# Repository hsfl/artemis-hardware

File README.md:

<br>

# Artemis Cubesat Kit Hardware

This repository contains CAD models, Eagle designs, and thermal analysis for the Artemis Cubesat Kit V1.

For documentation and tutorials, visit our [project website](https://sites.google.com/hawaii.edu/artemiscubesatkit).

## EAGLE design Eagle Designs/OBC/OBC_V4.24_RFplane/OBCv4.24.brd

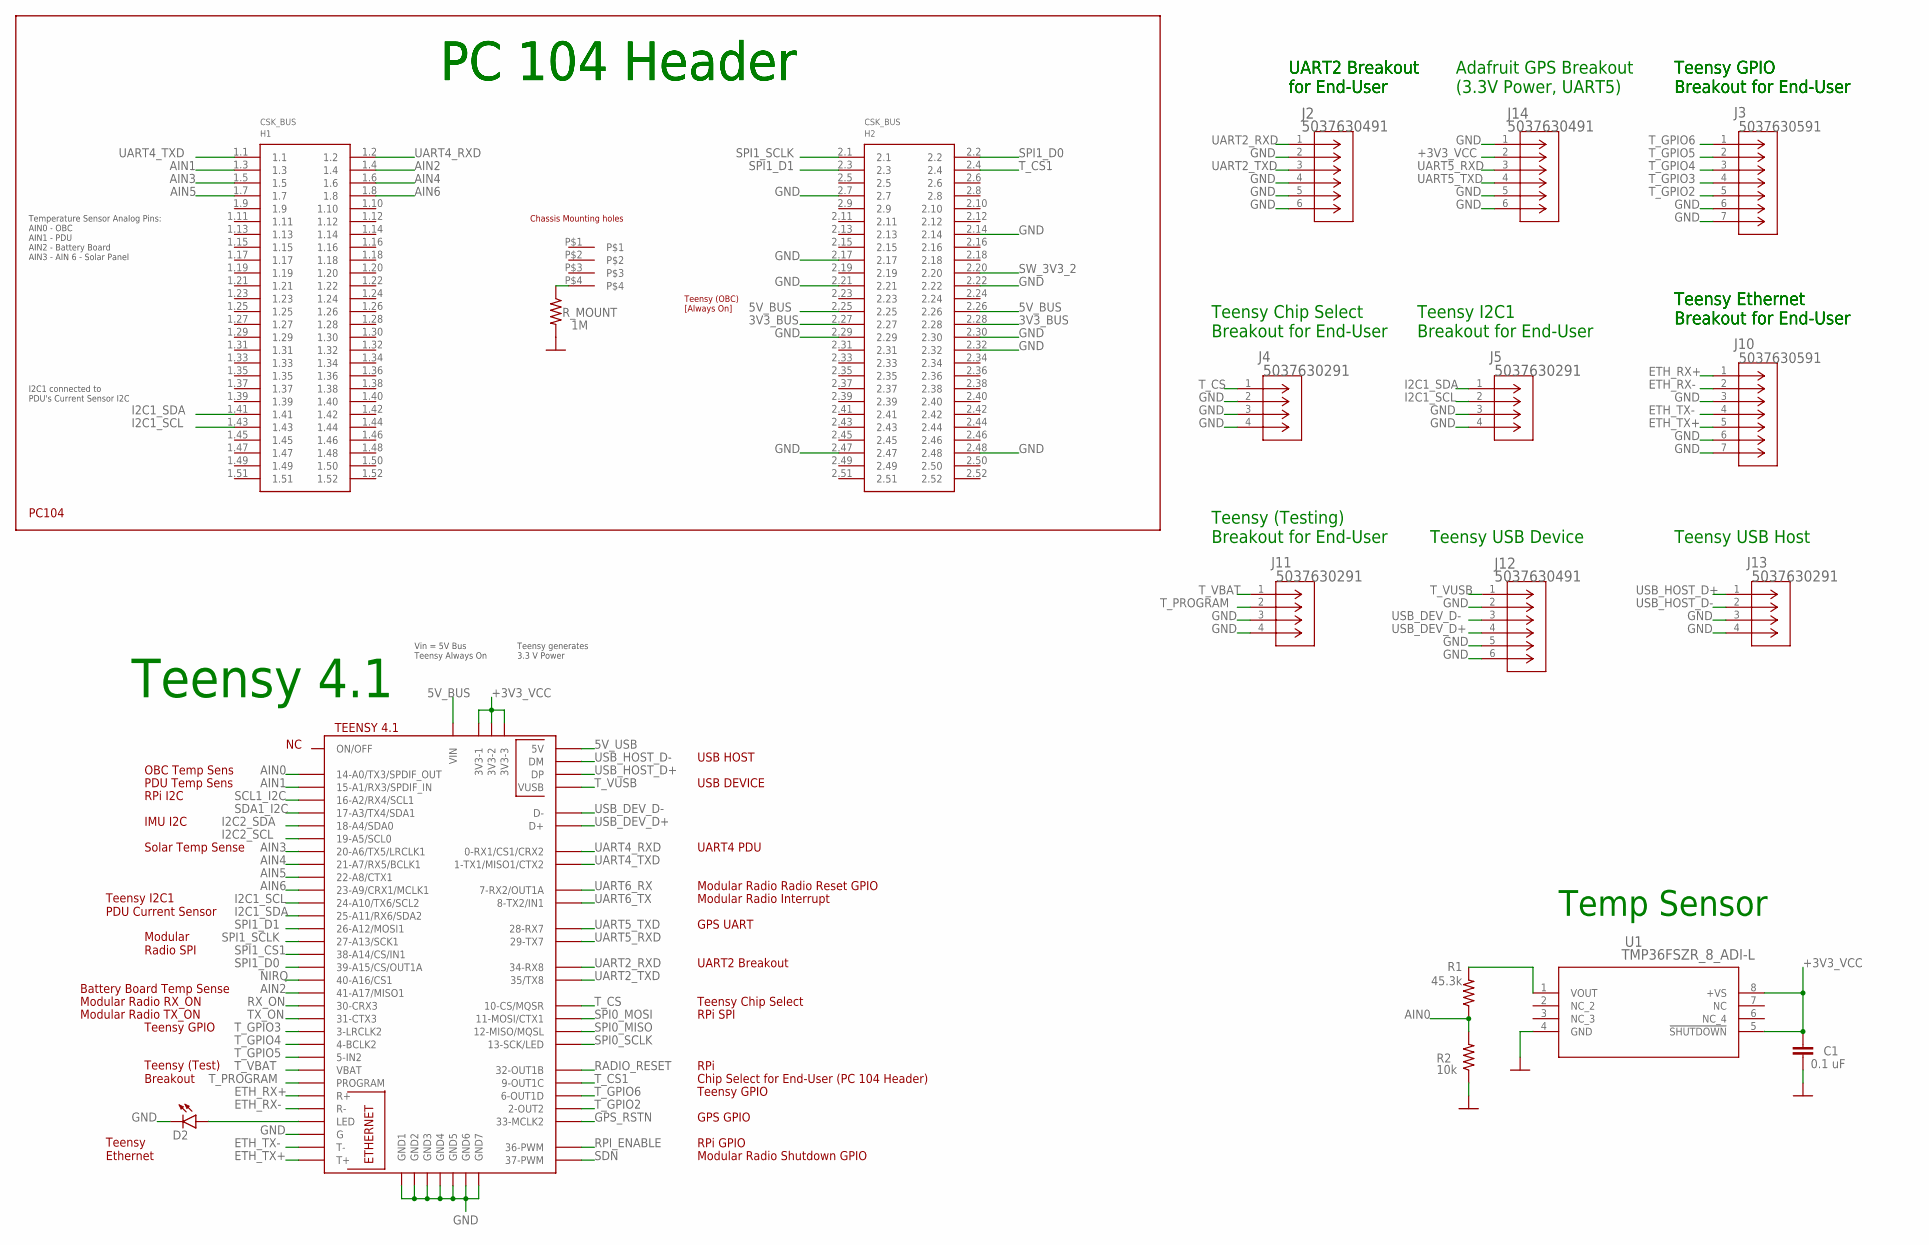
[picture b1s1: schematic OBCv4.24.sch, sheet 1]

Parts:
C1: 0.1 uF; 0805
D2: LEDCHIP-LED0603; CHIP-LED0603
H1: PC104_WCONN
J2, J12, J14: 5037630491; CON_5037630491
J3, J10: 5037630591; CON_5037630591
J4, J5, J11, J13: 5037630291; CON_5037630291
R1: 45.3k; 0805
R2: 10k; 0805
R_MOUNT: 1M; 0805
U1: TMP36FSZR_8_ADI-L; R_8_ADI-L
U$1: TEENSY41TEENSY; TEENSY41

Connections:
3V3_BUS: H1.2.27, H1.2.28; also elsewhere on the board
5V_BUS: H1.2.25, H1.2.26, U$1.VIN; also elsewhere on the board
5V_USB: U$1.+5V (5V)
+3V3_VCC: C1.1, J14.2, U1.5 (!SHUTDOWN), U1.8 (+VS), U$1.3V3-1, U$1.3V3-2, U$1.3V3-3; also elsewhere on the board
AIN0: R1.1, R2.2, U$1.14-A0/TX3/SPDIF_OUT
AIN1: H1.1.3, U$1.15-A1/RX3/SPDIF_IN
AIN2: H1.1.4, U$1.41-A17/MISO1
AIN3: H1.1.5, U$1.20-A6/TX5/LRCLK1
AIN4: H1.1.6, U$1.21-A7/RX5/BCLK1
AIN5: H1.1.7, U$1.22-A8/CTX1
AIN6: H1.1.8, U$1.23-A9/CRX1/MCLK1
ETH_RX+: J10.1, U$1.R+
ETH_RX-: J10.2, U$1.R-
ETH_TX+: J10.5, U$1.T+
ETH_TX-: J10.4, U$1.T-
GND: C1.2, D2.C, H1.2.7, H1.2.14, H1.2.17, H1.2.21, H1.2.22, H1.2.29, H1.2.30, H1.2.32, H1.2.47, H1.2.48, J2.2, J2.4, J2.5, J2.6, J3.6, J3.7, J4.2, J4.3, J4.4, J5.3, J5.4, J10.3, J10.6, J10.7, J11.3, J11.4, J12.2, J12.5, J12.6, J13.3, J13.4, J14.1, J14.5, J14.6, R2.1, R_MOUNT.2, U1.4 (GND), U$1.G, U$1.GND (GND7), U$1.GND1, U$1.GND2, U$1.GND3, U$1.GND4, U$1.GND5, U$1.GND6; also elsewhere on the board
GPS_RSTN: U$1.33-MCLK2; also elsewhere on the board
I2C1_SCL: H1.1.43, J5.2, U$1.24-A10/TX6/SCL2
I2C1_SDA: H1.1.41, J5.1, U$1.25-A11/RX6/SDA2
I2C2_SCL: U$1.19-A5/SCL0; also elsewhere on the board
I2C2_SDA: U$1.18-A4/SDA0; also elsewhere on the board
unnamed: D2.A, U$1.LED
unnamed: R1.2, U1.1 (VOUT)
unnamed: H1.P$4, R_MOUNT.1
NIRQ: U$1.40-A16/CS1; also elsewhere on the board
RADIO_RESET: U$1.32-OUT1B; also elsewhere on the board
RPI_ENABLE: U$1.36-PWM; also elsewhere on the board
RX_ON: U$1.30-CRX3; also elsewhere on the board
SCL1_I2C: U$1.16-A2/RX4/SCL1; also elsewhere on the board
SDA1_I2C: U$1.17-A3/TX4/SDA1; also elsewhere on the board
SDN: U$1.37-PWM; also elsewhere on the board
SPI0_MISO: U$1.12-MISO/MQSL; also elsewhere on the board
SPI0_MOSI: U$1.11-MOSI/CTX1; also elsewhere on the board
SPI0_SCLK: U$1.13-SCK/LED; also elsewhere on the board
SPI1_CS1: U$1.38-A14/CS/IN1; also elsewhere on the board
SPI1_D0: H1.2.2, U$1.39-A15/CS/OUT1A; also elsewhere on the board
SPI1_D1: H1.2.3, U$1.26-A12/MOSI1; also elsewhere on the board
SPI1_SCLK: H1.2.1, U$1.27-A13/SCK1; also elsewhere on the board
SW_3V3_2: H1.2.20; also elsewhere on the board
TX_ON: U$1.31-CTX3; also elsewhere on the board
T_CS: J4.1, U$1.10-CS\MQSR (10-CS/MQSR)
T_CS1: H1.2.4, U$1.9-OUT1C
T_GPIO2: J3.5, U$1.2-OUT2
T_GPIO3: J3.4, U$1.3-LRCLK2
T_GPIO4: J3.3, U$1.4-BCLK2
T_GPIO5: J3.2, U$1.5-IN2
T_GPIO6: J3.1, U$1.6-OUT1D
T_PROGRAM: J11.2, U$1.PROGRAM
T_VBAT: J11.1, U$1.VBAT
T_VUSB: J12.1, U$1.VUSB
UART2_RXD: J2.1, U$1.34-RX8
UART2_TXD: J2.3, U$1.35-TX8 (35/TX8)
UART4_RXD: H1.1.2, U$1.0-RX1/CS1/CRX2
UART4_TXD: H1.1.1, U$1.1-TX1/MISO1/CTX2
UART5_RXD: J14.3, U$1.29-TX7; also elsewhere on the board
UART5_TXD: J14.4, U$1.28-RX7; also elsewhere on the board
UART6_RX: U$1.7-RX2/OUT1A; also elsewhere on the board
UART6_TX: U$1.8-TX2/IN1; also elsewhere on the board
USB_DEV_D+: J12.4, U$1.D+
USB_DEV_D-: J12.3, U$1.D-
USB_HOST_D+: J13.1, U$1.DP
USB_HOST_D-: J13.2, U$1.DM

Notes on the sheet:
Temp Sensor
PC 104 Header
Temperature Sensor Analog Pins: AIN0 - OBC AIN1 - PDU AIN2 - Battery Board AIN3 - AIN 6 - Solar Panel
UART2 Breakout for End-User
Teensy 4.1
Teensy GPIO Breakout for End-User
Teensy Chip Select Breakout for End-User
Teensy I2C1 Breakout for End-User
OBC Temp Sens
PDU Temp Sens
RPi I2C
IMU I2C
Solar Temp Sense
Teensy I2C1 PDU Current Sensor
Modular Radio SPI
Battery Board Temp Sense
Teensy GPIO
Teensy (Test) Breakout
Teensy Ethernet
RPi GPIO
GPS GPIO
RPi SPI
Teensy Chip Select
UART2 Breakout
GPS UART
Modular Radio Radio Reset GPIO
UART4 PDU
USB HOST
USB DEVICE
Teensy Ethernet Breakout for End-User
Teensy (Testing) Breakout for End-User
Teensy USB Device
Teensy USB Host
Teensy (OBC) [Always On]
Vin = 5V Bus Teensy Always On
Teensy generates 3.3 V Power
Adafruit GPS Breakout (3.3V Power, UART5)
Modular Radio Interrupt
I2C1 connected to PDU's Current Sensor I2C
Chip Select for End-User (PC 104 Header)

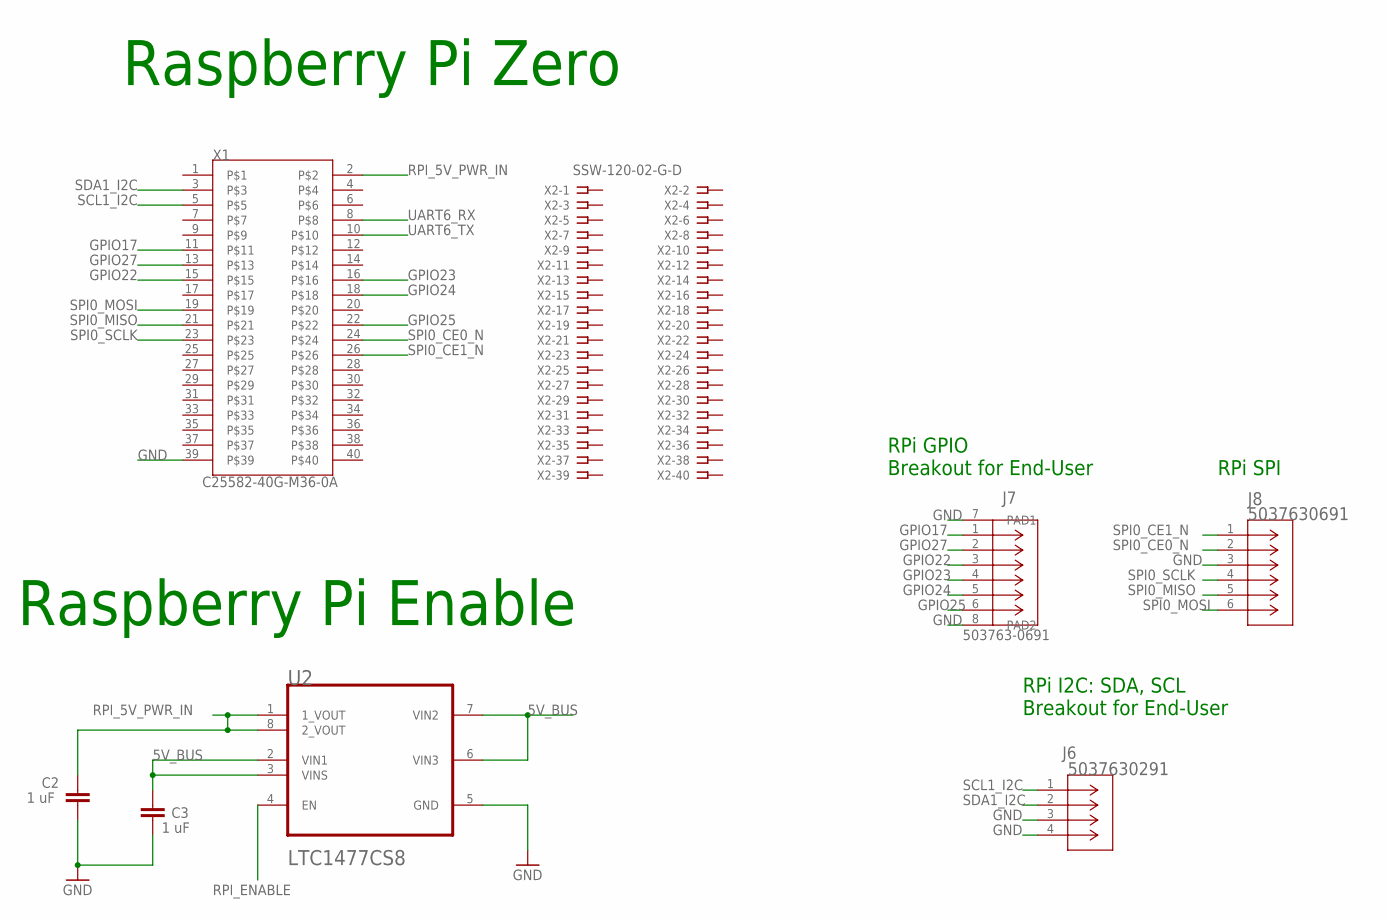
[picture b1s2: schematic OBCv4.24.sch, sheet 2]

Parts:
C2, C3: 1 uF; 0805
J6: 5037630291; CON_5037630291
J7: 503763-0691; CONN_503763-0691_MOL
J8: 5037630691; CONN_503763-0691_MOL
U2: LTC1477CS8LINEAR_TECHNOLOGY_LTC1477CS8_0_2; LINEAR_TECHNOLOGY_LTC1477CS8_2
X1: C25582-40G-M36-0A; ADAFRUIT_C25582-40G-M36-0A_0
X2: SSW-120-02-G-D

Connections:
5V_BUS: C3.1, U2.2 (VIN1), U2.3 (VINS), U2.6 (VIN3), U2.7 (VIN2); also elsewhere on the board
GND: C2.2, C3.2, J6.3, J6.4, J7.7 (PAD1), J7.8 (PAD2), J8.3, U2.5 (GND), X1.39; also elsewhere on the board
GPIO17: J7.1, X1.11
GPIO22: J7.3, X1.15
GPIO23: J7.4, X1.16
GPIO24: J7.5, X1.18
GPIO25: J7.6, X1.22
GPIO27: J7.2, X1.13
RPI_5V_PWR_IN: C2.1, U2.1 (1_VOUT), U2.8 (2_VOUT), X1.2
RPI_ENABLE: U2.4 (EN); also elsewhere on the board
SCL1_I2C: J6.1, X1.5; also elsewhere on the board
SDA1_I2C: J6.2, X1.3; also elsewhere on the board
SPI0_CE0_N: J8.2, X1.24
SPI0_CE1_N: J8.1, X1.26
SPI0_MISO: J8.5, X1.21; also elsewhere on the board
SPI0_MOSI: J8.6, X1.19; also elsewhere on the board
SPI0_SCLK: J8.4, X1.23; also elsewhere on the board
UART6_RX: X1.8; also elsewhere on the board
UART6_TX: X1.10; also elsewhere on the board

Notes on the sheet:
Raspberry Pi Zero
Raspberry Pi Enable
RPi I2C: SDA, SCL Breakout for End-User
RPi GPIO Breakout for End-User
RPi SPI

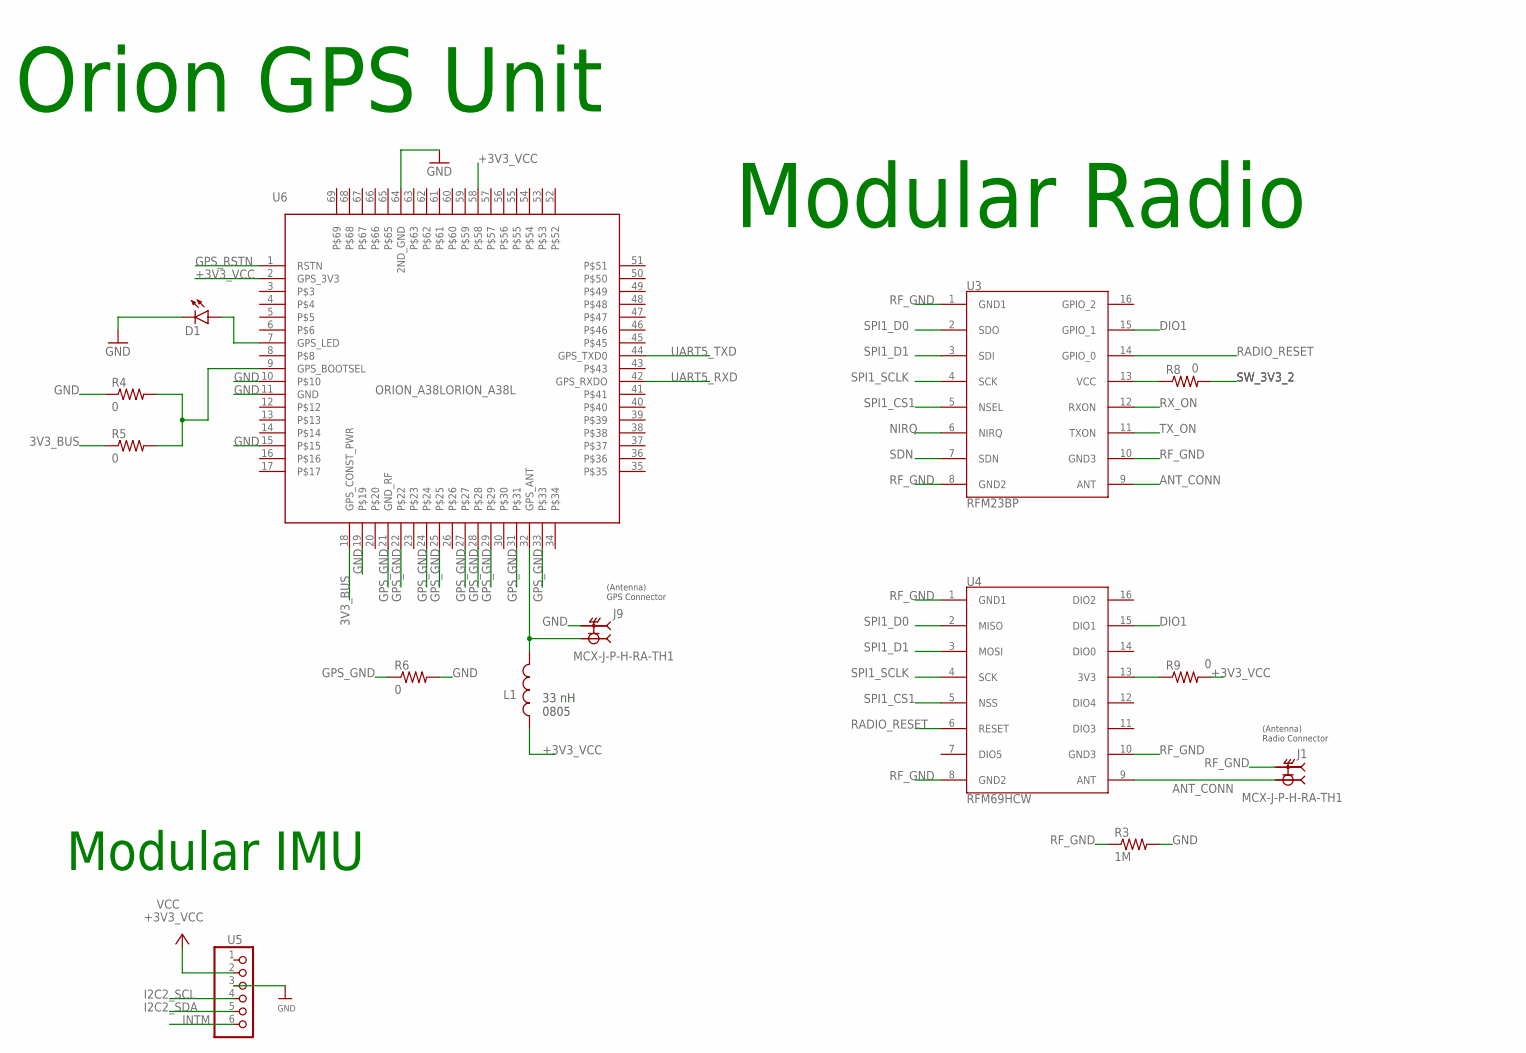
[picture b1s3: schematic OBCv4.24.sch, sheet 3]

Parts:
D1: LEDCHIP-LED0603; CHIP-LED0603
J1, J9: MCX-J-P-H-RA-TH1; SAMTEC_MCX-J-P-H-RA-TH1
L1: AIMC-0805-2N2S-T; INDC2012X105N
R3: 1M; 0805
R4, R5, R6: 0; 0805
R8, R9: 0; R2512
U3: RFM23BP
U4: RFM69HCW
U5: HEADER-1X670MIL; 1X06_ROUND_70
U6: ORION_A38LORION_A38L; ORION_A38L

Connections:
3V3_BUS: R5.1, U6.18 (GPS_CONST_PWR); also elsewhere on the board
+3V3_VCC: L1.1, R9.2, U5.2, U6.2 (GPS_3V3), U6.58; also elsewhere on the board
ANT_CONN: J1.1, U3.9 (ANT), U4.9 (ANT)
DIO1: U3.15 (GPIO_1), U4.15 (DIO1)
GND: D1.C, J9.S1 (2), J9.S2 (2), J9.S3 (2), J9.S4 (2), R3.2, R4.1, R6.2, U5.3, U6.10, U6.11 (GND), U6.15, U6.19, U6.64 (2ND_GND); also elsewhere on the board
GPS_GND: R6.1, U6.21 (GND_RF), U6.22, U6.24, U6.25, U6.27, U6.28, U6.29, U6.31, U6.33
GPS_RSTN: U6.1 (RSTN); also elsewhere on the board
I2C2_SCL: U5.4; also elsewhere on the board
I2C2_SDA: U5.5; also elsewhere on the board
INTM: U5.6
unnamed: R8.1, U3.13 (VCC)
unnamed: R9.1, U4.13 (3V3)
unnamed: R4.2, R5.2, U6.9 (GPS_BOOTSEL)
unnamed: J9.1, L1.2, U6.32 (GPS_ANT)
unnamed: D1.A, U6.7 (GPS_LED)
NIRQ: U3.6 (NIRQ); also elsewhere on the board
RADIO_RESET: U3.14 (GPIO_0), U4.6 (RESET); also elsewhere on the board
RF_GND: J1.S1 (2), J1.S2 (2), J1.S3 (2), J1.S4 (2), R3.1, U3.1 (GND1), U3.8 (GND2), U3.10 (GND3), U4.1 (GND1), U4.8 (GND2), U4.10 (GND3)
RX_ON: U3.12 (RXON); also elsewhere on the board
SDN: U3.7 (SDN); also elsewhere on the board
SPI1_CS1: U3.5 (NSEL), U4.5 (NSS); also elsewhere on the board
SPI1_D0: U3.2 (SDO), U4.2 (MISO); also elsewhere on the board
SPI1_D1: U3.3 (SDI), U4.3 (MOSI); also elsewhere on the board
SPI1_SCLK: U3.4 (SCK), U4.4 (SCK); also elsewhere on the board
SW_3V3_2: R8.2; also elsewhere on the board
TX_ON: U3.11 (TXON); also elsewhere on the board
UART5_RXD: U6.42 (GPS_RXDO); also elsewhere on the board
UART5_TXD: U6.44 (GPS_TXD0); also elsewhere on the board

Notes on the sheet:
Orion GPS Unit
Modular Radio
Modular IMU
(Antenna) Radio Connector
(Antenna) GPS Connector
33 nH 0805

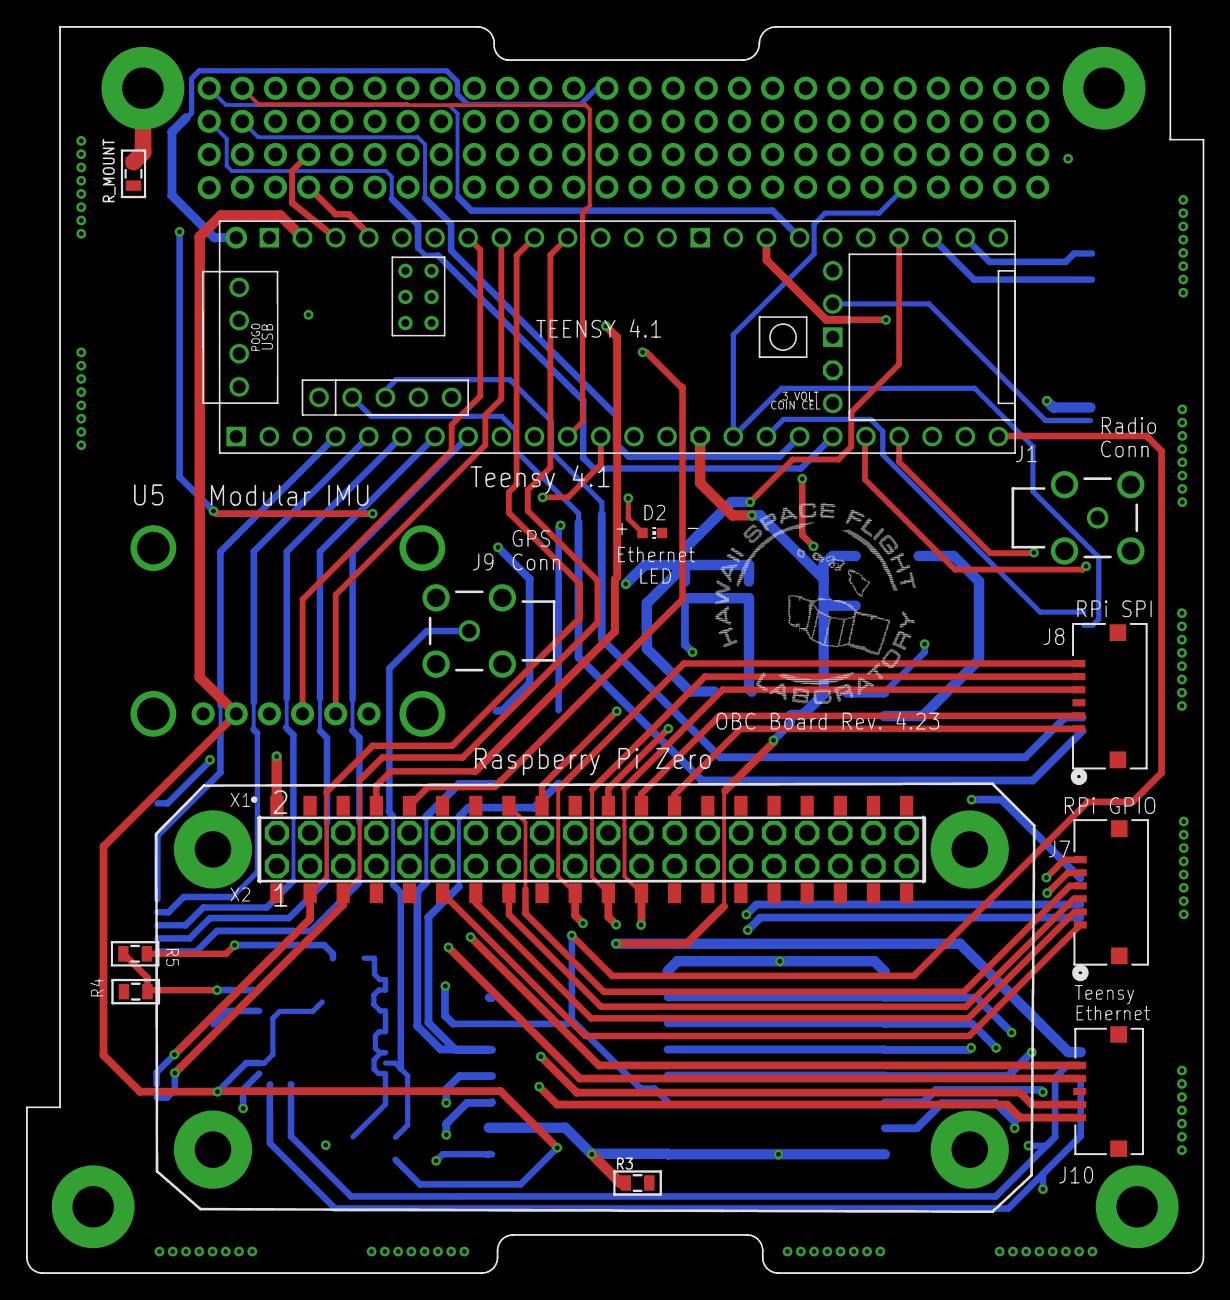
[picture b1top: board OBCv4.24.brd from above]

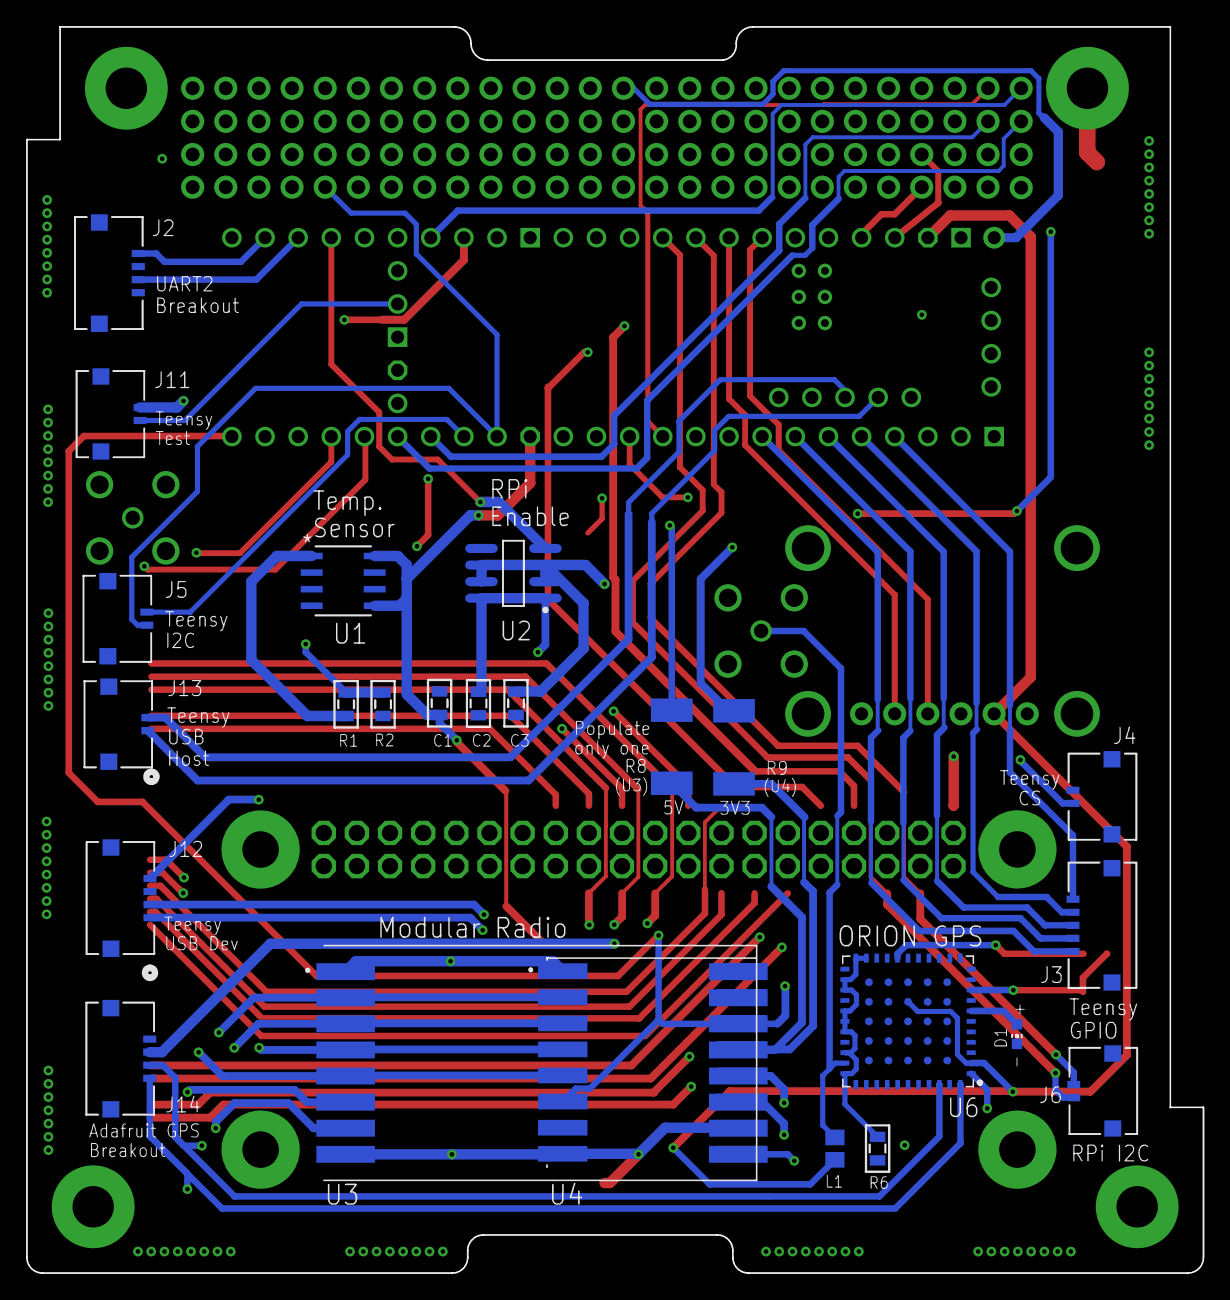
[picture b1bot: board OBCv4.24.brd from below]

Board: 4 copper layers, 90.2 x 95.5 mm, 39 parts (24 on the bottom side), 79 nets.

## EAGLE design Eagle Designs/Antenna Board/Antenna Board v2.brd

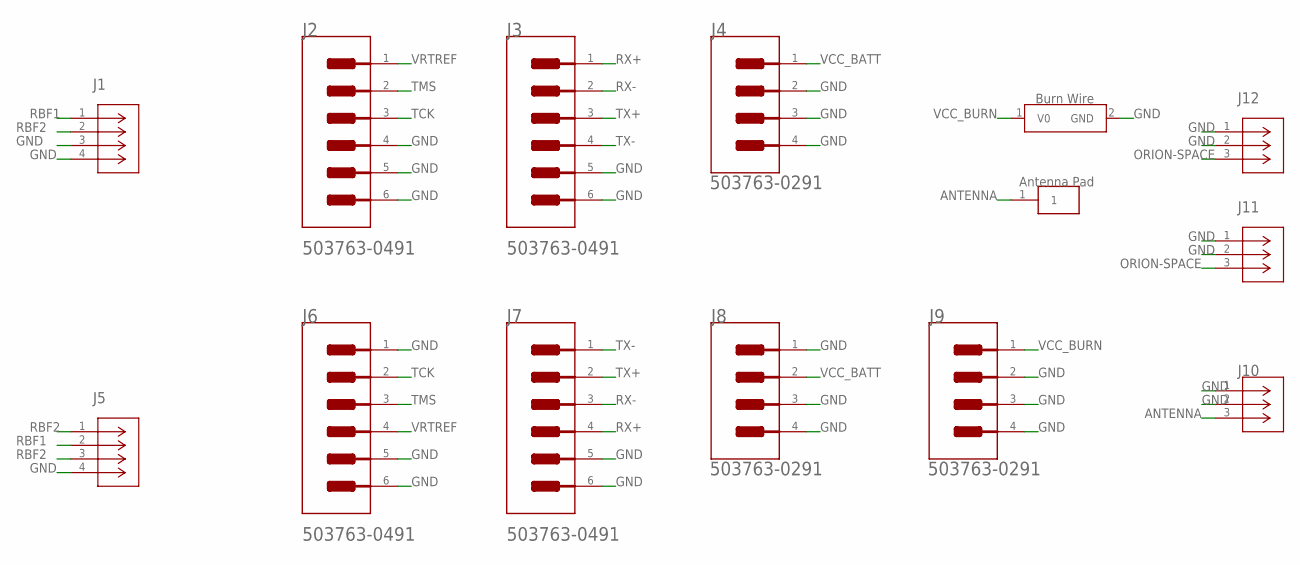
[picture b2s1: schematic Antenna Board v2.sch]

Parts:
J1, J5: 5037630291; CON_5037630291
J2, J3, J6, J7: MOLEX_503763-0491MOLEX_503763-0491_0_0; MOLEX_503763-0491_0
J4, J8, J9: MOLEX_503763-0291MOLEX_503763-0291_0_0; MOLEX_503763-0291_0
J10, J11, J12: U.FL-R-SMT-1(01); CONN_-SMT-1(01)
U$2: ANTENNA_PAD
U$3: BURNWIRE

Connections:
ANTENNA: J10.3, U$2.1
GND: J1.3, J1.4, J2.4, J2.5 (MNT_1), J2.6 (MNT_2), J3.5 (MNT_1), J3.6 (MNT_2), J4.2, J4.3 (MNT_1), J4.4 (MNT_2), J5.4, J6.1, J6.5 (MNT_1), J6.6 (MNT_2), J7.5 (MNT_1), J7.6 (MNT_2), J8.1, J8.3 (MNT_1), J8.4 (MNT_2), J9.2, J9.3 (MNT_1), J9.4 (MNT_2), J10.1, J10.2, J11.1, J11.2, J12.1, J12.2, U$3.2 (GND)
ORION-SPACE: J11.3, J12.3
RBF1: J1.1, J5.2
RBF2: J1.2, J5.1, J5.3
RX+: J3.1, J7.4
RX-: J3.2, J7.3
TCK: J2.3, J6.2
TMS: J2.2, J6.3
TX+: J3.3, J7.2
TX-: J3.4, J7.1
VCC_BATT: J4.1, J8.2
VCC_BURN: J9.1, U$3.1 (V0)
VRTREF: J2.1, J6.4

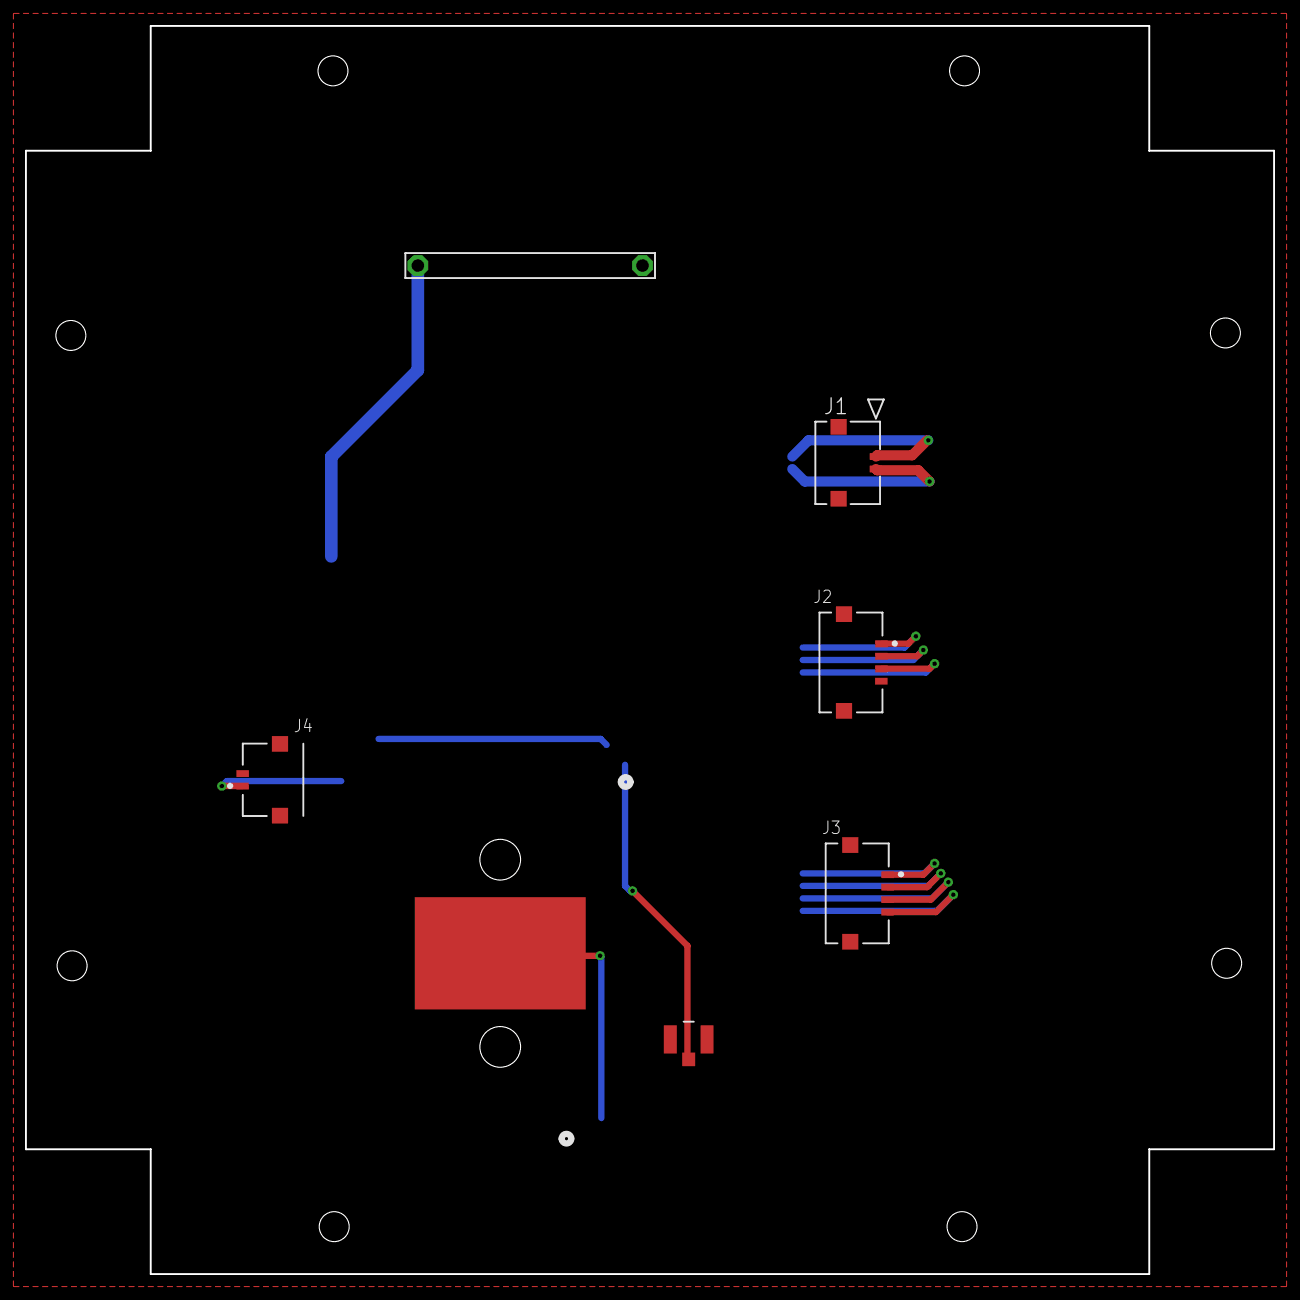
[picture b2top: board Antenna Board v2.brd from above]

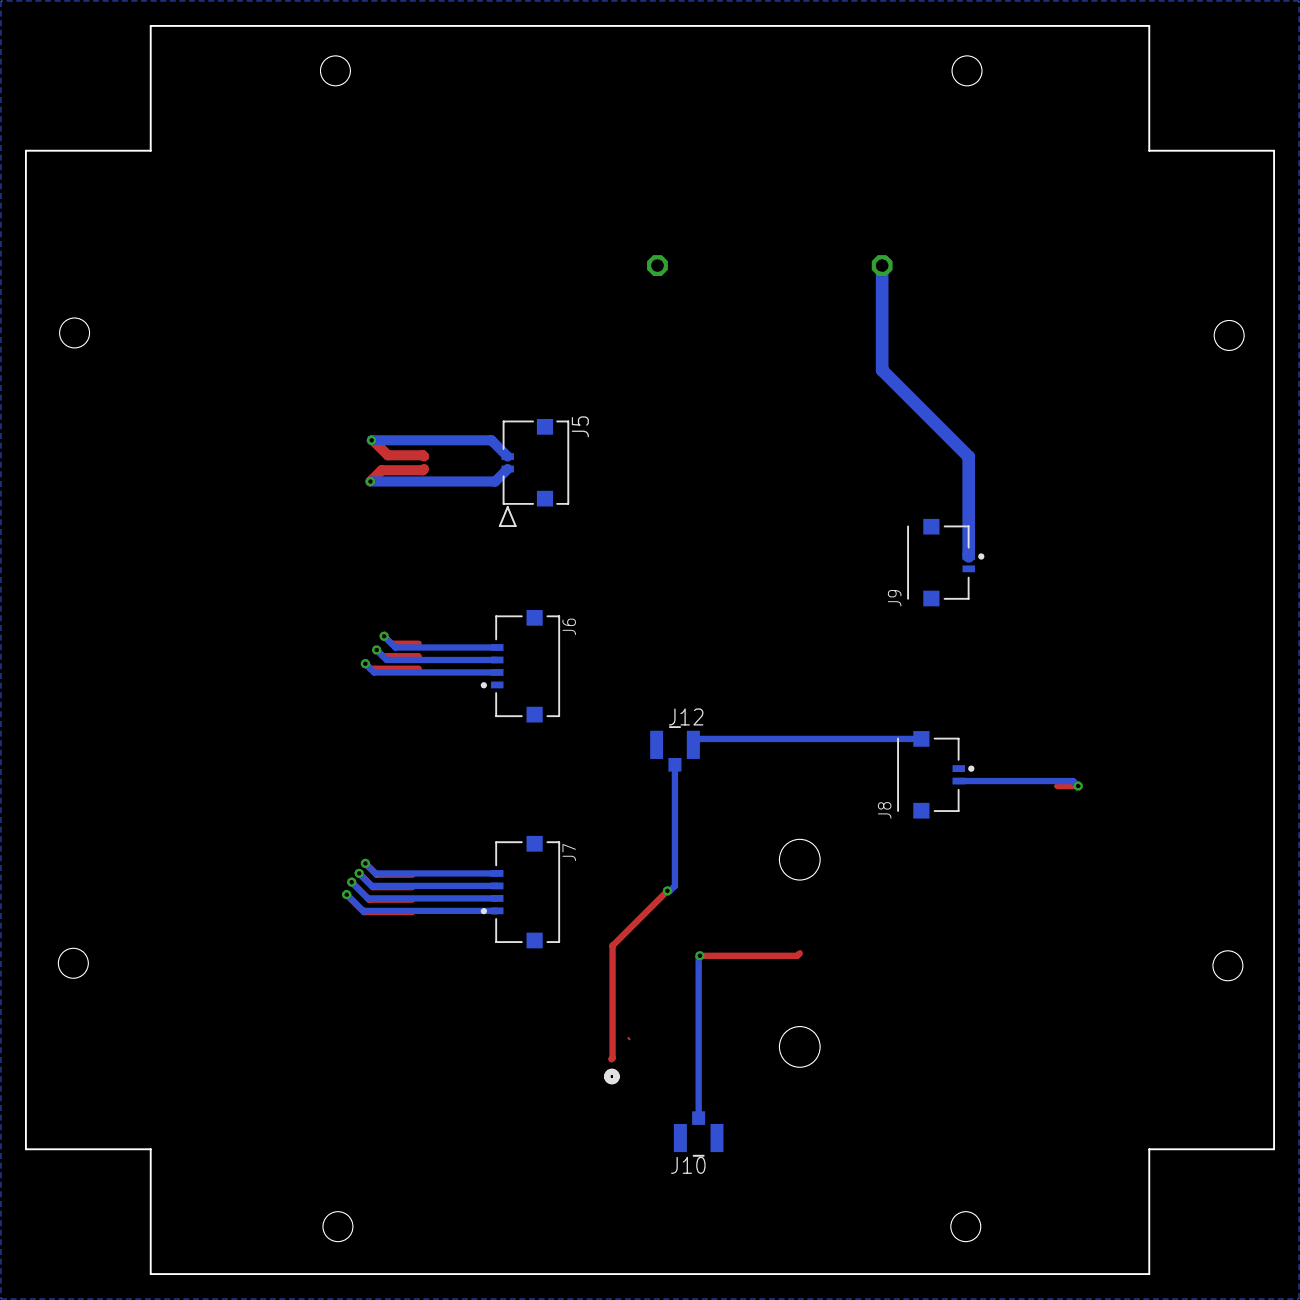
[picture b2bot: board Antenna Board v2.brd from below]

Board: 2 copper layers, 100.0 x 100.0 mm, 14 parts (7 on the bottom side), 14 nets.

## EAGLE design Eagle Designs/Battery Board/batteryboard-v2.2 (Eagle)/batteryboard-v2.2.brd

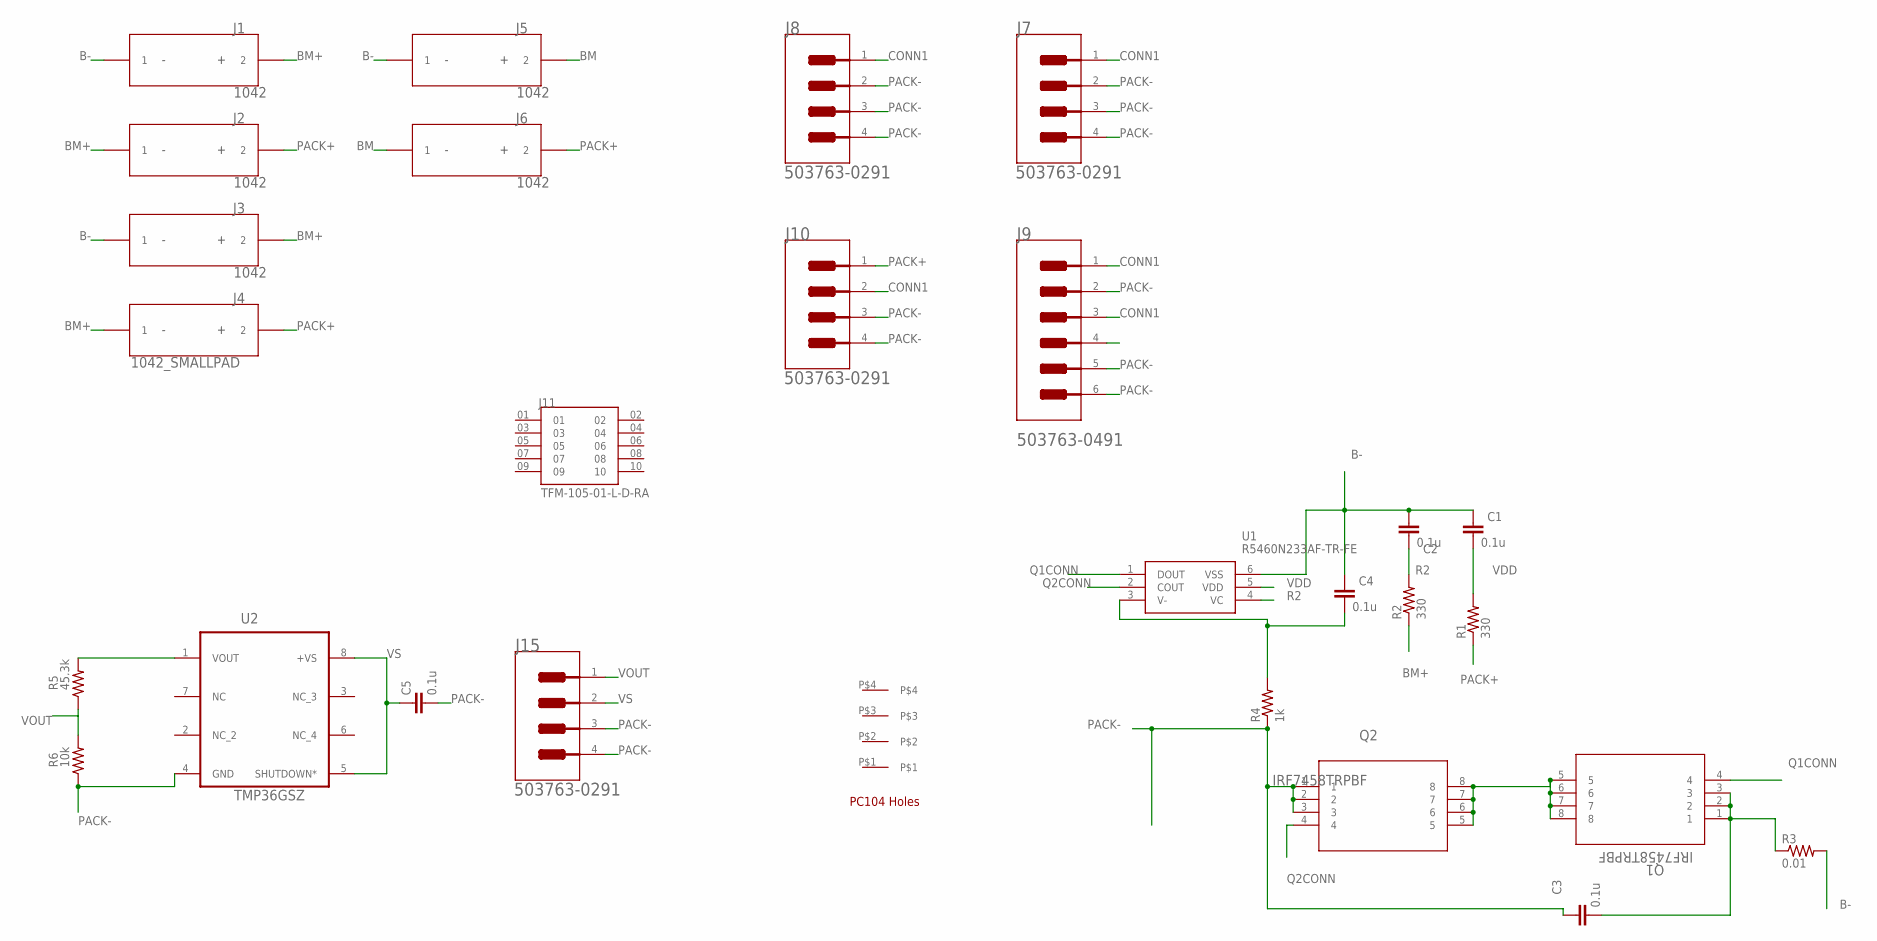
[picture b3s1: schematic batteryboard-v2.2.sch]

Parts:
C1, C2, C3, C4: 0.1u; 0603-CAP
C5: 0.1u; 0805
J1, J2, J3, J5, J6: 1042; 1042_KEY
J4: 1042_SMALLPAD; 1042_KEY_SMALLPAD
J7, J8, J10, J15: MOLEX_503763-0291MOLEX_503763-0291_0_0; MOLEX_503763-0291_0
J9: MOLEX_503763-0491MOLEX_503763-0491_0_0; MOLEX_503763-0491_0
J11: TFM-105-01-L-D-RA; SAMTEC_TFM-105-01-L-D-RA
Q1, Q2: IRF7458TRPBF; SO-8_IRF7458_3P9X4P9_INF
R1, R2: 330; 0603-RES
R3: 0.01; R2512
R4: 1k; 0603-RES
R5: 45.3k; 0805
R6: 10k; 0805
U1: R5460N233AF-TR-FE; SOT95P280X140-6N
U2: TMP36GSZ; SOIC127P600X175-8N
U$1: PC104_HOLES

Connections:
B-: C1.1, C2.1, C4.1, J1.1, J3.1, J5.1, R3.2, U1.6 (VSS)
BM: J5.2, J6.1
BM+: J1.2, J2.1, J3.2, J4.1, R2.1
CONN1: J7.1, J8.1, J9.1, J9.3, J10.2
unnamed: R5.2, U2.1 (VOUT)
unnamed: C3.2, Q1.1, Q1.2, Q1.3, R3.1
unnamed: C4.2, R4.2, U1.3 (V-)
unnamed: Q1.5, Q1.6, Q1.7, Q1.8, Q2.5, Q2.6, Q2.7, Q2.8
PACK+: J2.2, J4.2, J6.2, J10.1, R1.1
PACK-: C3.1, C5.2, J7.2, J7.3 (MNT_1), J7.4 (MNT_2), J8.2, J8.3 (MNT_1), J8.4 (MNT_2), J9.2, J9.4, J9.5 (MNT_1), J9.6 (MNT_2), J10.3 (MNT_1), J10.4 (MNT_2), J15.3 (MNT_1), J15.4 (MNT_2), Q2.1, Q2.2, Q2.3, R4.1, R6.1, U2.4 (GND)
Q1CONN: Q1.4, U1.1 (DOUT)
Q2CONN: Q2.4, U1.2 (COUT)
R2: C2.2, R2.2, U1.4 (VC)
VDD: C1.2, R1.2, U1.5 (VDD)
VOUT: J15.1, R5.1, R6.2
VS: C5.1, J15.2, U2.5 (SHUTDOWN*), U2.8 (+VS)

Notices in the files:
parts and their libraries:
COPYRIGHT: Copyright (C) 2018 Accelerated Designs. All rights reserved
COPYRIGHT: Copyright (C) 2021 Ultra Librarian. All rights reserved.
microbuilder: This work is placed in the public domain, and may be freely used for commercial and non-commercial work with the following conditions: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
